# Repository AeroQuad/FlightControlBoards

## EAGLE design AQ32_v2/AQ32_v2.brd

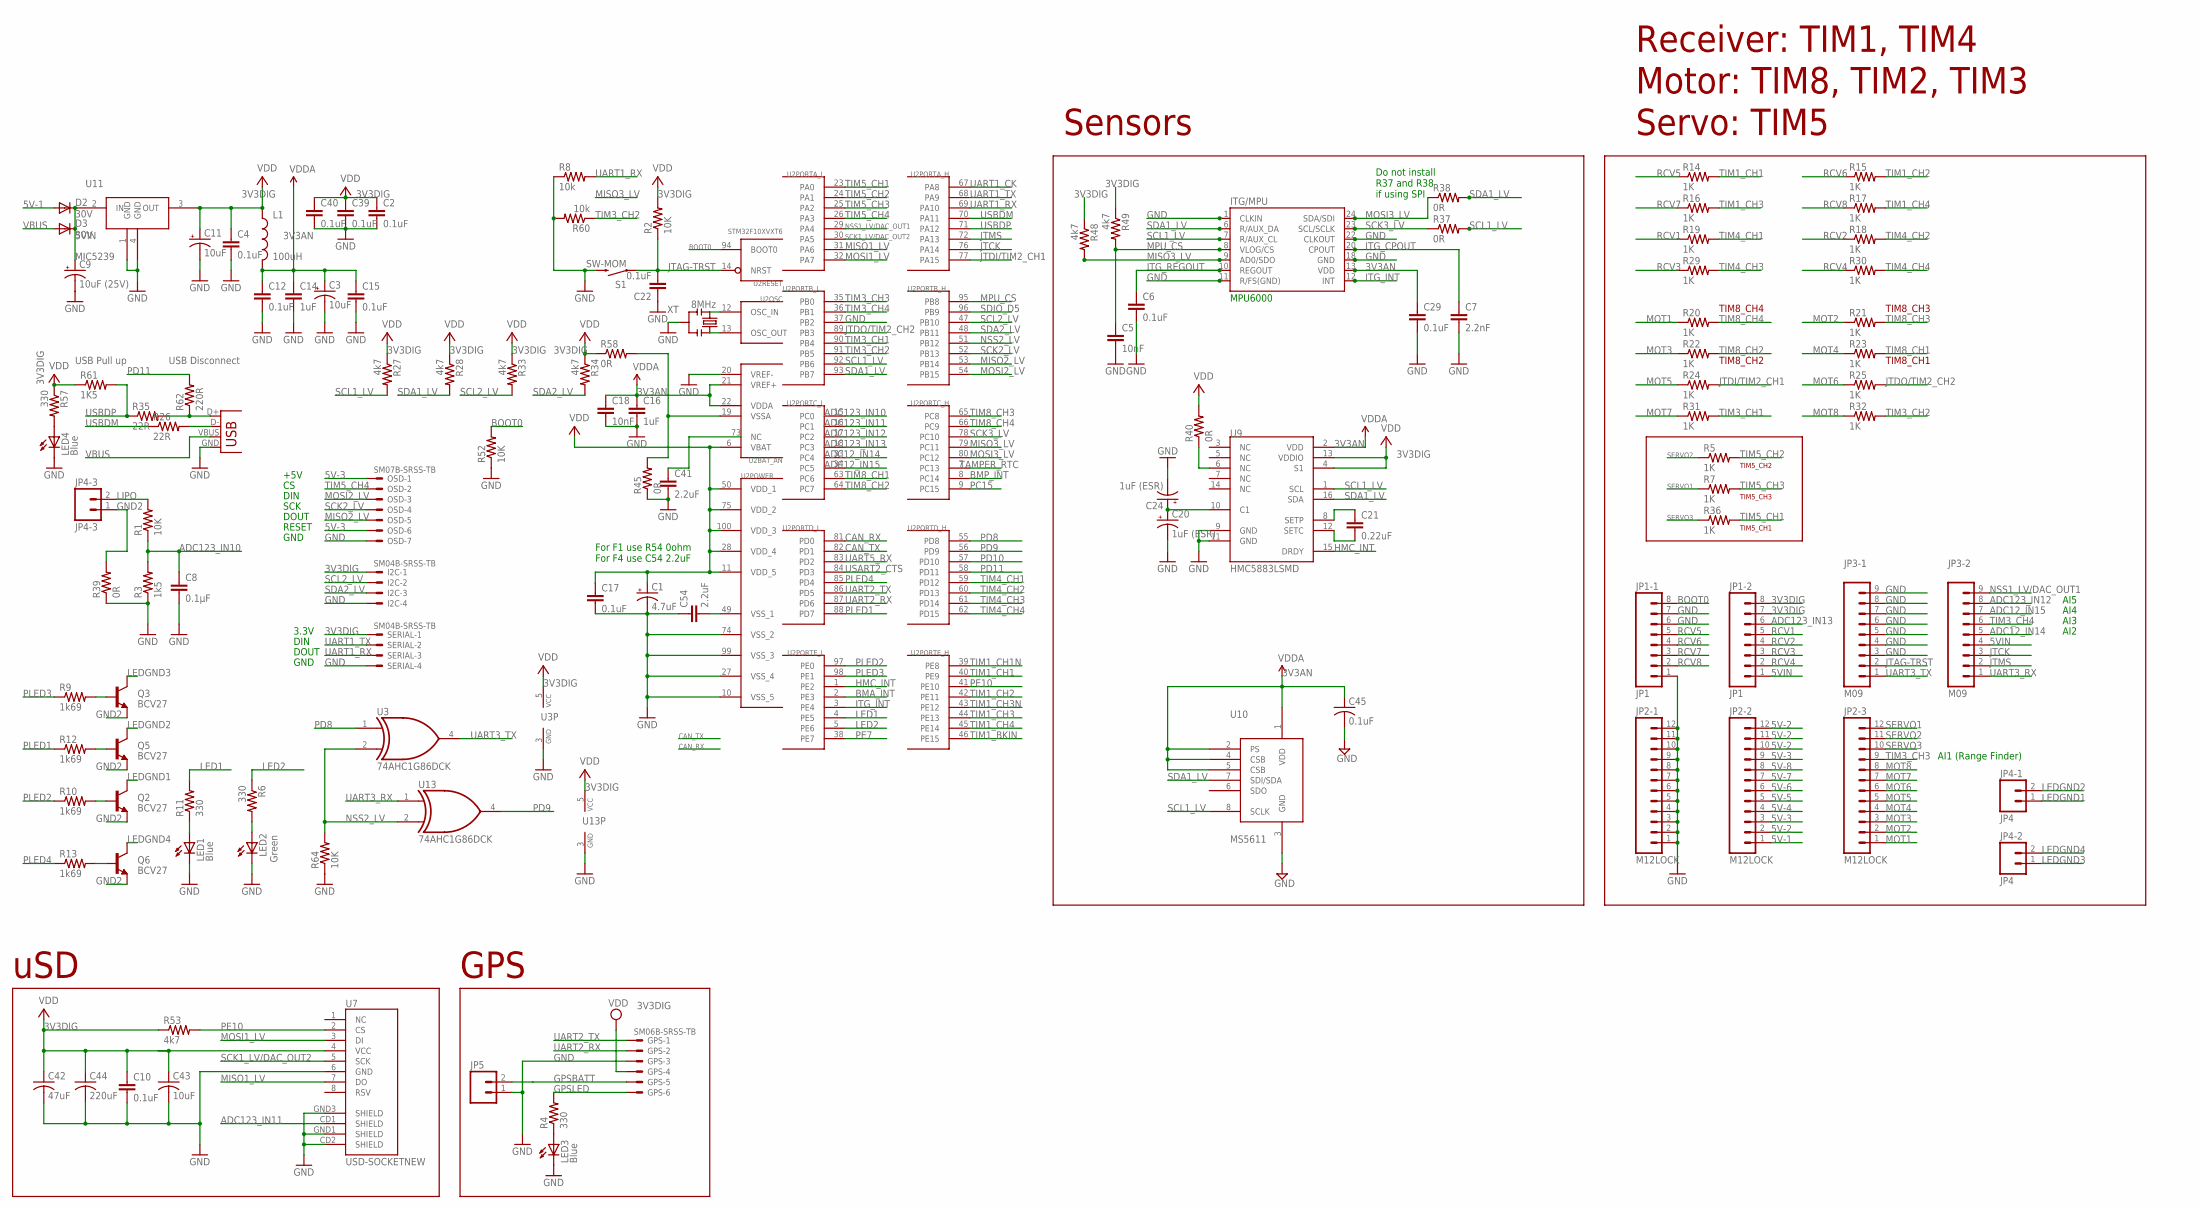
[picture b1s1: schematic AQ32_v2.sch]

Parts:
C1: 4.7uF; SMC_Z
C2, C4, C6, C10, C12, C15, C17, C22, C29, C39, C40, C45: 0.1uF; C0402
C3, C11: 10uF; EIA3216
C5, C18: 10nF; C0402
C7: 2.2nF; C0402
C8: 0.1µF; C0402
C9: 10uF (25V); EIA3216
C14, C16: 1uF; C0402
C20, C24: 1uF (ESR); SMC_Z
C21: 0.22uF; C0402
C41: 2.2uF; C0402
C42: 47uF; C0805
C43: 10uF; C0805
C44: 220uF; C1206
C54: 2.2uF; 0402-CAP
D2, D3: 30V; SOD-323
GPS: SM06B-SRSS-TB
I2C: SM04B-SRSS-TB
JP1-1, JP1-2: JP1; 1X08_LOCK
JP2-1, JP2-2, JP2-3: M12LOCK; 1X12_LOCK
JP3-1, JP3-2: M09; 1X09
JP4-1, JP4-2: JP4; 1X02
JP4-3: JP4-3; 1X02
JP5: M02PTH; 1X02
L1: 100uH; 0805
LED1, LED3, LED4: Blue; LED-0603
LED2: Green; LED-0603
OSD: SM07B-SRSS-TB
Q2, Q3, Q5, Q6: BCV27; SOT23-3
R1, R2, R52, R64: 10K; C0402
R3: 1k5; C0402
R4, R6, R11, R57: 330; C0402
R5, R7, R14, R15, R16, R17, R18, R19, R20, R21, R22, R23, R24, R25, R29, R30, R31, R32, R36: 1K; C0402
R8, R60: 10k; R0402
R9, R10, R12, R13: 1k69; C0402
R26, R35: 22R; C0402
R27, R28, R33, R34, R48, R49, R53: 4k7; C0402
R37, R38, R40, R45, R58: 0R; R0402
R39: 0R; C0402
R61: 1K5; R0402
R62: 220R; C0402
S1: SW-MOM; TACTILE_SWITCH_SMD
SERIAL: SM04B-SRSS-TB
U1: ITG-3200; QFN-24
U2: STM32F10XVXT6; TQFP100
U3, U13: 74AHC1G86DCK; SC70-5
U7: USD-SOCKETNEW; MICRO-SD-SOCKET-PP
U9: HMC5883LSMD; 16LPCC
U10: MS5611; LGA08A
U11: MIC5239; TO-223
X2: USBOLD; USB-MINIB-OLD
XT: 8MHz; RESONATOR-SMD

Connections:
3V3AN: C3.A (+), C12.1, C14.1, C15.1, C16.1, C18.1, C29.1, C45.1, L1.2, U1.13 (VDD), U2.21 (VREF+), U2.22 (VDDA), U9.2 (VDD), U10.1 (VDD), U10.2 (PS), U10.4 (CSB), U10.5 (CSB)
3V3DIG: C1.+, C2.1, C4.1, C10.1, C11.A (+), C17.1, C39.1, C40.1, C42.1, C43.1, C44.1, GPS.4, I2C.1, JP1-2.7, JP1-2.8, L1.1, R2.2, R27.1, R28.1, R33.1, R34.1, R40.2, R48.1, R49.1, R53.1, R57.1, R58.1, R61.1, SERIAL.1, U2.6 (VBAT), U2.11 (VDD_5), U2.28 (VDD_4), U2.50 (VDD_1), U2.75 (VDD_2), U2.100 (VDD_3), U3.5 (VCC), U7.4 (VCC), U9.4 (S1), U9.13 (VDDIO), U11.3 (OUT), U13.5 (VCC)
5V-1: D2.2 (A), JP2-2.1
5V-2: JP2-2.2, JP2-2.10, JP2-2.11, JP2-2.12
5V-3: JP2-2.3, JP2-2.9, OSD.1, OSD.6
5V-4: JP2-2.4
5V-5: JP2-2.5
5V-6: JP2-2.6
5V-7: JP2-2.7
5V-8: JP2-2.8
5VIN: C9.A (+), D2.1 (C), D3.1 (C), JP1-2.1, JP3-2.4, U11.2 (IN)
ADC12_IN14: JP3-2.5, U2.33 (PC4)
ADC12_IN15: JP3-2.7, U2.34 (PC5)
ADC123_IN10: C8.1, R1.1, R3.2, U2.15 (PC0)
ADC123_IN11: U2.16 (PC1), U7.CD1 (SHIELD)
ADC123_IN12: JP3-2.8, U2.17 (PC2)
ADC123_IN13: JP1-2.6, U2.18 (PC3)
BMA_INT: U2.2 (PE3)
BMP_INT: U2.8 (PC14)
BOOT0: JP1-1.8, R52.2, U2.94 (BOOT0)
CAN_RX: U2.81 (PD0)
CAN_TX: U2.82 (PD1)
GND: C1.-, C2.2, C3.C (-), C4.2, C5.2, C6.2, C7.2, C8.2, C9.C (-), C10.2, C11.C (-), C12.2, C14.2, C15.2, C16.2, C17.2, C18.2, C20.-, C22.1, C24.-, C29.2, C39.2, C40.2, C41.2, C42.2, C43.2, C44.2, C45.2, C54.1, GPS.3, I2C.4, JP1-1.1, JP1-1.6, JP1-1.7, JP2-1.1, JP2-1.2, JP2-1.3, JP2-1.4, JP2-1.5, JP2-1.6, JP2-1.7, JP2-1.8, JP2-1.9, JP2-1.10, JP2-1.11, JP2-1.12, JP3-1.3, JP3-1.4, JP3-1.5, JP3-1.6, JP3-1.7, JP3-1.8, JP3-1.9, JP5.1, LED1.C, LED2.C, LED3.C, LED4.C, OSD.7, R3.1, R8.1, R39.1, R45.1, R52.1, R60.2, R64.1, S1.3 (2), SERIAL.4, U1.1 (CLKIN), U1.11 (R/FS(GND)), U1.18 (GND), U1.22 (CLKOUT), U2.10 (VSS_5), U2.20 (VREF-), U2.27 (VSS_4), U2.37 (PB2), U2.74 (VSS_2), U2.99 (VSS_3), U3.3 (GND), U7.6 (GND)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
GND2: JP4-3.1, Q2.2 (E), Q3.2 (E), Q5.2 (E), Q6.2 (E), R39.2
GPSBATT: GPS.5, JP5.2
GPSLED: GPS.6, R4.2
HMC_INT: U2.1 (PE2), U9.15 (DRDY)
ITG_CPOUT: C7.1, U1.20 (CPOUT)
ITG_INT: U1.12 (INT), U2.3 (PE4)
ITG_REGOUT: C6.1, U1.10 (REGOUT)
JTAG-TRST: C22.2, JP3-1.2, R2.1, S1.1, U2.14 (NRST)
JTCK: JP3-2.3, U2.76 (PA14)
JTDI/TIM2_CH1: R24.2, U2.77 (PA15)
JTDO/TIM2_CH2: R25.2, U2.89 (PB3)
JTMS: JP3-2.2, U2.72 (PA13)
LED1: R11.2, U2.4 (PE5)
LED2: R6.1, U2.5 (PE6)
LEDGND1: JP4-1.1, Q2.3 (C)
LEDGND2: JP4-1.2, Q5.3 (C)
LEDGND3: JP4-2.1, Q3.3 (C)
LEDGND4: JP4-2.2, Q6.3 (C)
LIPO: JP4-3.2, R1.2
MISO1_LV: U2.31 (PA6), U7.7 (DO)
MISO2_LV: OSD.5, U2.53 (PB14)
MISO3_LV: R48.2, U1.9 (AD0/SDO), U2.79 (PC11)
MOSI1_LV: U2.32 (PA7), U7.3 (DI)
MOSI2_LV: OSD.3, U2.54 (PB15)
MOSI3_LV: R38.1, U1.24 (SDA/SDI), U2.80 (PC12)
MOT1: JP2-3.1, R20.1
MOT2: JP2-3.2, R21.1
MOT3: JP2-3.3, R22.1
MOT4: JP2-3.4, R23.1
MOT5: JP2-3.5, R24.1
MOT6: JP2-3.6, R25.1
MOT7: JP2-3.7, R31.1
MOT8: JP2-3.8, R32.1
MPU_CS: C5.1, R49.2, U1.8 (VLOG/CS), U2.95 (PB8)
unnamed: U2.12 (OSC_IN), XT.3
unnamed: U2.13 (OSC_OUT), XT.1
unnamed: LED3.A, R4.1
unnamed: R40.1, U9.6 (NC)
unnamed: LED2.A, R6.2
unnamed: Q3.1 (B), R9.2
unnamed: C54.2, U2.49 (VSS_1)
unnamed: Q2.1 (B), R10.2
unnamed: Q5.1 (B), R12.2
unnamed: LED1.A, R11.1
unnamed: Q6.1 (B), R13.2
unnamed: C41.1, U2.73 (NC)
unnamed: LED4.A, R57.2
unnamed: R45.2, R58.2, U2.19 (VSSA)
unnamed: C21.1, U9.8 (SETP)
unnamed: C21.2, U9.12 (SETC)
unnamed: C20.+, C24.+, U9.10 (C1)
unnamed: R35.2, R62.1, X2.D+
unnamed: R26.2, X2.D-
NSS1_LV/DAC_OUT1: JP3-2.9, U2.29 (PA4)
NSS2_LV: R64.2, U2.51 (PB12), U3.2 (I1), U13.2 (I1)
PC15: U2.9 (PC15)
PD8: U2.55 (PD8), U3.1 (I0)
PD9: U2.56 (PD9), U13.4 (O)
PD10: U2.57 (PD10)
PD11: R62.2, U2.58 (PD11)
PE7: U2.38 (PE7)
PE10: R53.2, U2.41 (PE10), U7.2 (CS)
PLED1: R12.1, U2.88 (PD7)
PLED2: R10.1, U2.97 (PE0)
PLED3: R9.1, U2.98 (PE1)
PLED4: R13.1, U2.85 (PD4)
RCV1: JP1-2.5, R19.1
RCV2: JP1-2.4, R18.1
RCV3: JP1-2.3, R29.1
RCV4: JP1-2.2, R30.1
RCV5: JP1-1.5, R14.1
RCV6: JP1-1.4, R15.1
RCV7: JP1-1.3, R16.1
RCV8: JP1-1.2, R17.1
SCK1_LV/DAC_OUT2: U2.30 (PA5), U7.5 (SCK)
SCK2_LV: OSD.4, U2.52 (PB13)
SCK3_LV: R37.1, U1.23 (SCL/SCLK), U2.78 (PC10)
SCL1_LV: R27.2, R37.2, U1.7 (R/AUX_CL), U2.92 (PB6), U9.1 (SCL), U10.8 (SCLK)
SCL2_LV: I2C.2, R33.2, U2.47 (PB10)
SDA1_LV: R28.2, R38.2, U1.6 (R/AUX_DA), U2.93 (PB7), U9.16 (SDA), U10.7 (SDI/SDA)
SDA2_LV: I2C.3, R34.2, U2.48 (PB11)
SDIO_D5: U2.96 (PB9)
SERVO1: JP2-3.12, R7.1
SERVO2: JP2-3.11, R5.1
SERVO3: JP2-3.10, R36.1
TAMPER_RTC: U2.7 (PC13)
TIM1_BKIN: U2.46 (PE15)
TIM1_CH1: R14.2, U2.40 (PE9)
TIM1_CH1N: U2.39 (PE8)
TIM1_CH2: R15.2, U2.42 (PE11)
TIM1_CH3: R16.2, U2.44 (PE13)
TIM1_CH3N: U2.43 (PE12)
TIM1_CH4: R17.2, U2.45 (PE14)
TIM3_CH1: R31.2, U2.90 (PB4)
TIM3_CH2: R32.2, R60.1, U2.91 (PB5)
TIM3_CH3: JP2-3.9, U2.35 (PB0)
TIM3_CH4: JP3-2.6, U2.36 (PB1)
TIM4_CH1: R19.2, U2.59 (PD12)
TIM4_CH2: R18.2, U2.60 (PD13)
TIM4_CH3: R29.2, U2.61 (PD14)
TIM4_CH4: R30.2, U2.62 (PD15)
TIM5_CH1: R36.2, U2.23 (PA0)
TIM5_CH2: R5.2, U2.24 (PA1)
TIM5_CH3: R7.2, U2.25 (PA2)
TIM5_CH4: OSD.2, U2.26 (PA3)
TIM8_CH1: R23.2, U2.63 (PC6)
TIM8_CH2: R22.2, U2.64 (PC7)
TIM8_CH3: R21.2, U2.65 (PC8)
TIM8_CH4: R20.2, U2.66 (PC9)
UART1_CK: U2.67 (PA8)
UART1_RX: R8.2, SERIAL.3, U2.69 (PA10)
UART1_TX: SERIAL.2, U2.68 (PA9)
UART2_RX: GPS.2, U2.87 (PD6)
UART2_TX: GPS.1, U2.86 (PD5)
UART3_RX: JP3-2.1, U13.1 (I0)
UART3_TX: JP3-1.1, U3.4 (O)
UART5_RX: U2.83 (PD2)
USART2_CTS: U2.84 (PD3)
USBDM: R26.1, U2.70 (PA11)
USBDP: R35.1, R61.2, U2.71 (PA12)
VBUS: D3.2 (A), X2.VBUS

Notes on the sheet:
Receiver: TIM1, TIM4
Motor: TIM8, TIM2, TIM3
Servo: TIM5
USB Pull up
USB Disconnect
MPU6000
Sensors
uSD
GPS
TIM8_CH4
TIM8_CH1
TIM8_CH3
TIM8_CH2
TIM5_CH2
TIM5_CH1
TIM5_CH3
+5V
DIN
SCK
DOUT
RESET
GND
3.3V
AI1 (Range Finder)
AI2
AI3
AI4
AI5
Do not install R37 and R38 if using SPI
For F1 use R54 0ohm For F4 use C54 2.2uF

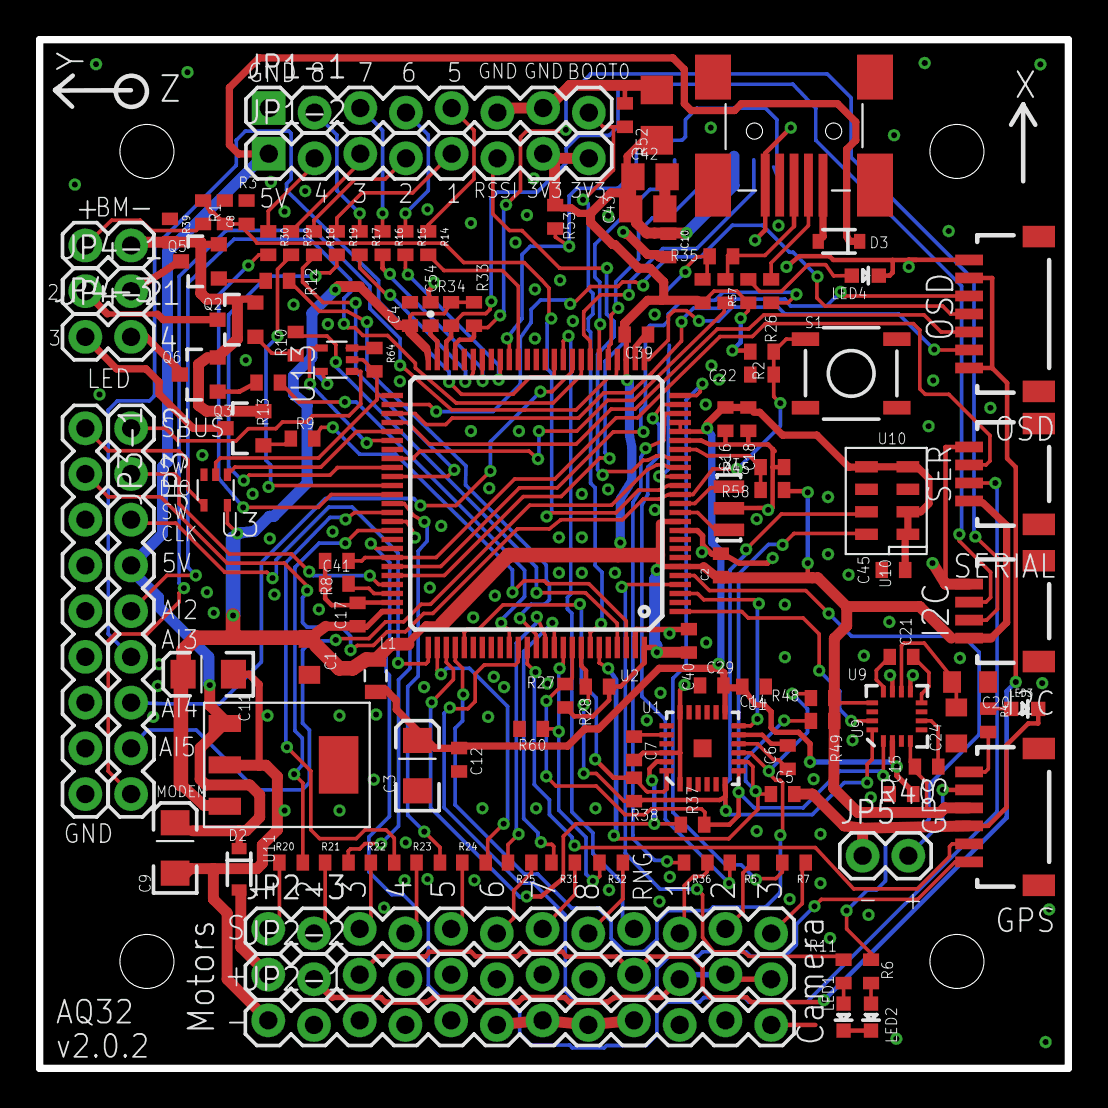
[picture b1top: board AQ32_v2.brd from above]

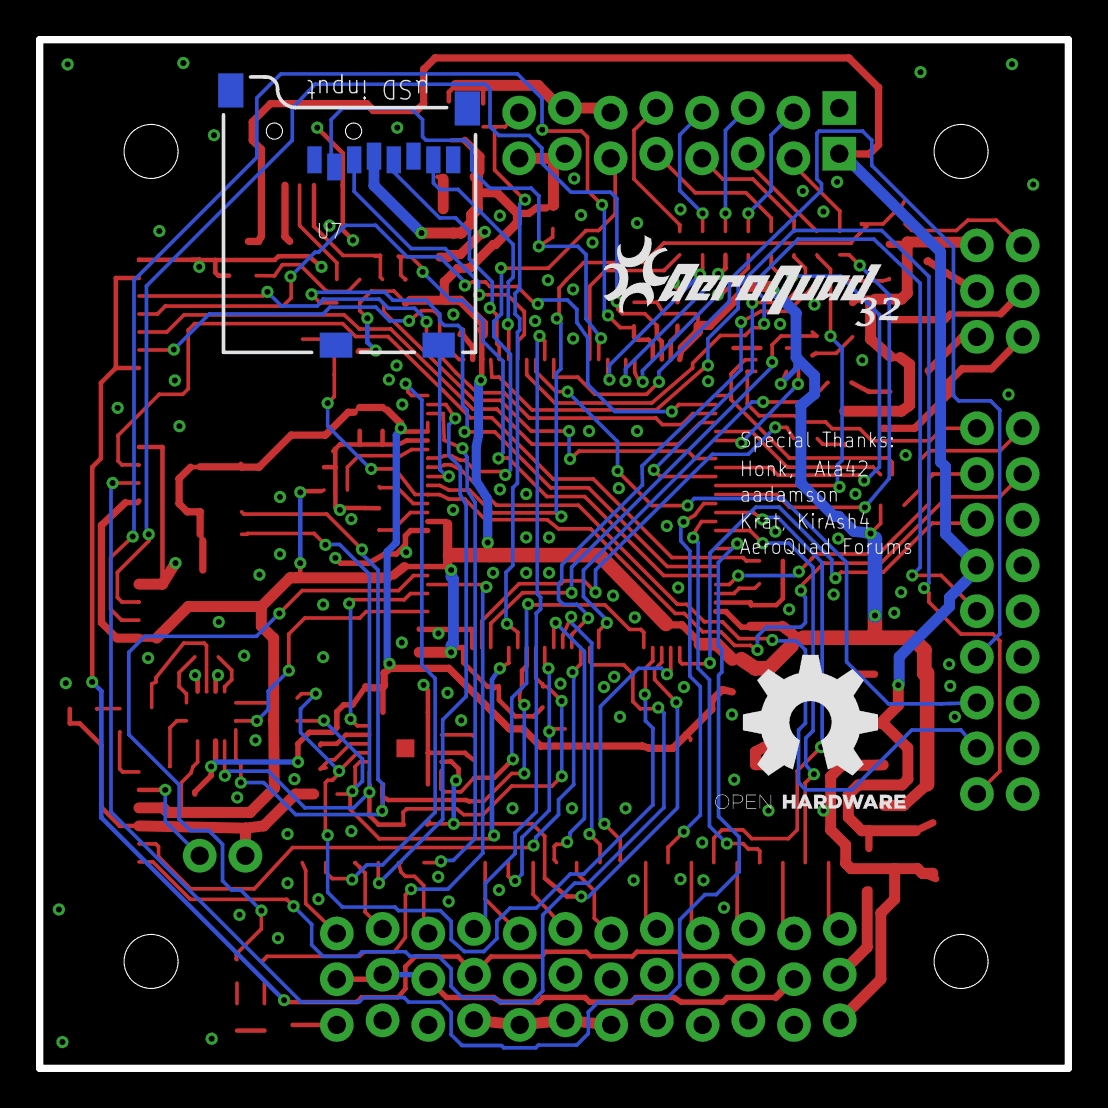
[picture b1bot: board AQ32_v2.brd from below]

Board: 2 copper layers, 57.1 x 57.1 mm, 120 parts (3 on the bottom side), 124 nets.

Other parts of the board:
U$4: AQ-WORDS-PT07
U$5: OSHW_TEXT

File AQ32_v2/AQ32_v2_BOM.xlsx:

Item # | Qty | Ref Des | Description | Package | Value | Device
1 | 2 | R54, R58 | Resistor | R0402 | 0R | R-US_R0402
2 | 6 | R1, R2, R8, R52, R60, R64 | Resistor | R0402 | 10k | RESISTOR0402
3 | 19 | R5, R7, R14, R15, R16, R17, R18, R19, R20, R21, R22, R23, R24, R25, R29, R30, R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 | Resistor | R0402 | 1k | RESISTOR0402
4 | 2 | R3, R61 | Resistor | R0402 | 1k5 | R-US_R0402
5 | 4 | R9, R10, R12, R13 | Resistor | R0402 | 1k69 | RESISTOR0402
6 | 1 | R62 | Resistor | R0402 | 220R | RESISTOR0402
7 | 2 | R26, R35 | Resistor | R0402 | 22R | RESISTOR0402
8 | 4 | R4, R6, R11, R57 | Resistor | R0402 | 330 | RESISTOR0402
9 | 7 | R27, R28, R33, R34, R48, R49, R53 | Resistor | R0402 | 4k7 | RESISTOR0402
10 | 11 | C4, C6, C8, C12, C15, C17, C22, C29, C39, C40, C45 | Capacitor | C0402 | 0.1uF | CAP0402
11 | 1 | C21 | Capacitor | C0402 | 0.22uF | CAP0402
12 | 1 | C18 | Capacitor | C0402 | 10nF | CAP0402
13 | 1 | C43 | Capacitor | C0805 | 10uF | C-USC0805
14 | 2 | C3, C11 | Capacitor Polarized | EIA3216 | 10uF | CAP_POL1206
15 | 1 | C9 | Capacitor Polarized | EIA3216 | 10uF (25V) | CAP_POL1206
16 | 2 | C14, C16 | Capacitor | C0402 | 1uF | CAP0402
17 | 2 | C20, C24 | Capacitor Polarized | SMC_Z | 1uF (ESR) | CPOL-USSMCZ
18 | 1 | C7 | Capacitor | C0402 | 2.2nF | CAP0402
19 | 1 | C41 | Capacitor | C0402 | 2.2uF | CAP0402
20 | 1 | C44 | Capacitor | C1206 | 220uF | C-USC1206
21 | 1 | C1 | Capacitor Polarized | SMC_Z | 4.7uF | CPOL-USSMCZ
22 | 1 | C42 | Capacitor | C0805 | 47uF | C-USC0805
23 | 2 | D2, D3 | Diode | SOD-323 | 30V | DIODESOD
24 | 1 | L1 | Inductors | 805 | 100uH | INDUCTOR0805
25 | 1 | L2 | Inductors | 805 | 22uH | INDUCTOR0805
26 | 1 | XT | Resonator | RESONATOR-SMD | 8MHz | RESONATORSMD
27 | 4 | Q2, Q3, Q5, Q6 | Transistor NPN | SOT23-3 | BCV27 | TRANSISTOR_NPNSOT23-3
28 | 3 | LED1, LED3, LED4 | LEDs | LED-0603 | Blue | LED0603
29 | 1 | LED2 | LEDs | LED-0603 | Green | LED0603
30 | 2 | U3, U13 | 2-input EXCLUSIV-OR gate | SC70-5 | 74AHC1G86DCK | 74AHC1G86DCK
31 | 1 | U9 | 3 Axis Digital Compass IC | 16LPCC | HMC5883LSMD | HMC5883LSMD
32 | 1 | U11 | LDO 3.3V Volt Reg | TO-223 | MIC5239 | MIC5239
33 | 2 | I2C, SERIAL | Disconnectable Crimp style connector, 1.0mm pitch4 contacts | SM04B-SRSS-TB | SM04B-SRSS-TB | SM04B-SRSS-TB
34 | 1 | GPS | Disconnectable Crimp style connector, 1.0mm pitch6 contacts | SM06B-SRSS-TB | SM06B-SRSS-TB | SM06B-SRSS-TB
35 | 1 | OSD | Disconnectable Crimp style connector, 1.0mm pitch7 contacts | SM07B-SRSS-TB | SM07B-SRSS-TB | SM07B-SRSS-TB
36 | 1 | U2 | STM32F407VGT6 | TQFP100 | STM32F407VGT6 | STM32F407VGT6
37 | 1 | S1 | SWITCH TACTILE SPST-NO 0.05A 12V | TACTILE_SWITCH_SMD | SW-MOM | SWITCH-MOMENTARY-2SMD
38 | 1 | X2 | USB Connectors | USB-MINIB-OLD | USBOLD | USBOLD
39 | 1 | U7 | microSD Socket | MICRO-SD-SOCKET-PP | USD-SOCKETNEW | USD-SOCKETNEW
40 | 1 | JP1 | 2x8 Right Angle Male Header | 2x08 | JP1 | M08LOCK
41 | 1 | JP3-1, JP3-2 | Do Not Install | Do Not Install | Do Not Install | Do Not Install
42 | 1 | JP4-1, JP4-2 | Do Not Install | Do Not Install | Do Not Install | Do Not Install
43 | 2 | JP5, JP6 | Do Not Install | Do Not Install | Do Not Install | Do Not Install
44 | 1 | C5 | Do Not Install | Do Not Install | Do Not Install | Do Not Install
45 | 2 | R37, R38, R45 | Do Not Install | Do Not Install | Do Not Install | Do Not Install
46 | 1 | JP2 | 3x12 Right Angle Male Header | 3x12 | M12LOCK | M12LOCK
47 | 1 | U1 | MPU-6000 6DOF IMU | QFN-24 | MPU-6000 | MPU-6000
48 | 1 | U10 | Pressure sensor 10cm | LGA08A | MS5611 | MS5611

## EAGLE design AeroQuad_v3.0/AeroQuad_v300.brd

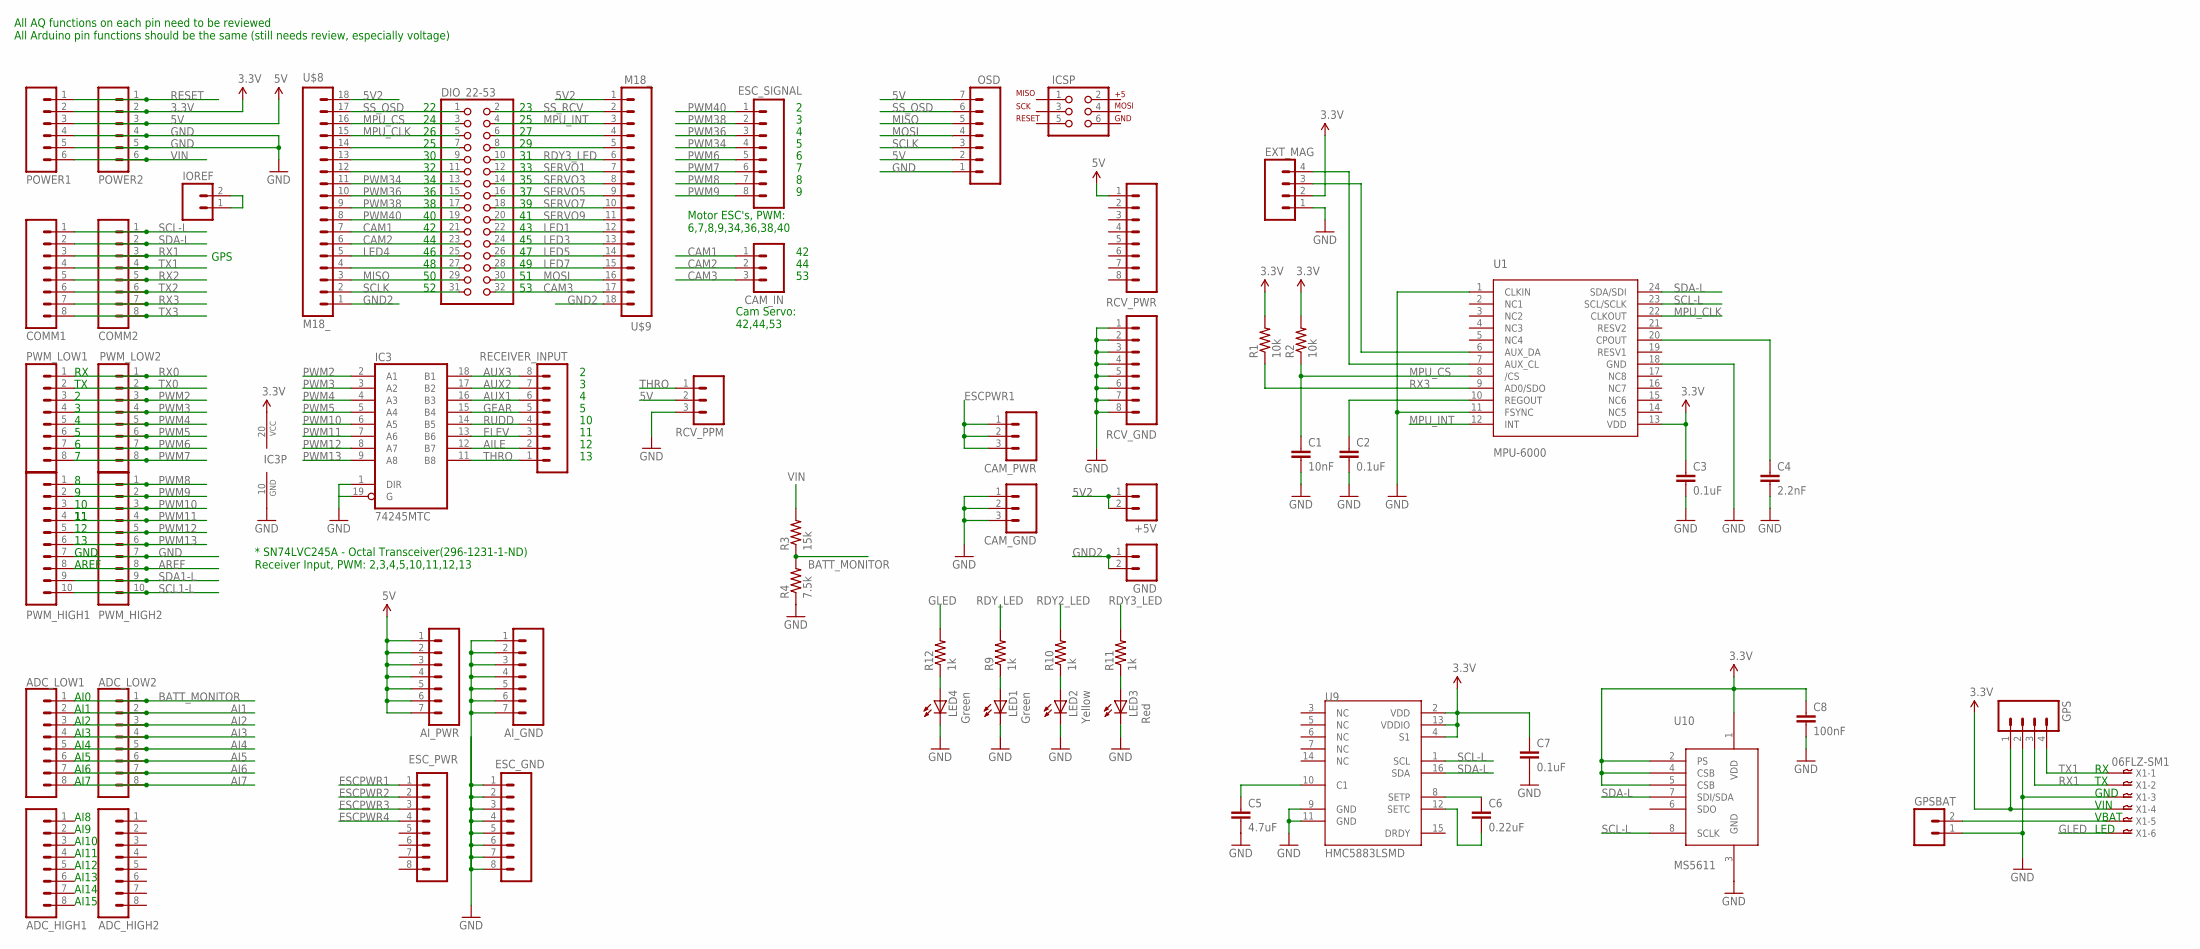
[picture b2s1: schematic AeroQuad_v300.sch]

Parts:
+5V: M02PTH; 1X02
ADC_HIGH1, ADC_HIGH2: M08LOCK; 1X08_LOCK
ADC_LOW1, ADC_LOW2: M08LOCK; 1X08_LOCK
AI_GND: M07; 1X07
AI_PWR: M07; 1X07
C1: 10nF; 0402-CAP
C2, C3, C7: 0.1uF; 0402-CAP
C4: 2.2nF; 0402-CAP
C5: 4.7uF; 0402-CAP
C6: 0.22uF; 0402-CAP
C8: 100nF; 0402-CAP
CAM_GND: M03LOCK; 1X03_LOCK
CAM_IN: M03LOCK; 1X03_LOCK
CAM_PWR: M03LOCK; 1X03_LOCK
COMM1, COMM2: M08LOCK; 1X08_LOCK
DIO_22-53: PINHD-2X16; 2X16
ESC_GND: M11LOCK; 1X08_LOCK
ESC_PWR: M11LOCK; 1X08_LOCK
ESC_SIGNAL: M11LOCK; 1X08_LOCK
EXT_MAG: M04LOCK; 1X04_LOCK
GND: M02PTH; 1X02
GPS: M04LOCK; 1X04_LOCK
GPSBAT: M02PTH; 1X02
IC3: 74245MTC; SSOP20
ICSP: AVR_SPI_PRG_6NS; 2X3-NS
IOREF: M02LOCK; 1X02_LOCK
LED1, LED4: Green; LED-0603
LED2: Yellow; LED-0603
LED3: Red; LED-0603
OSD: M07LOCK; 1X07_LOCK
POWER1, POWER2: M06LOCK; 1X06_LOCK
PWM_HIGH1, PWM_HIGH2: M10LOCK; 1X10_LOCK
PWM_LOW1, PWM_LOW2: M08LOCK; 1X08_LOCK
R1, R2: 10k; 0402-RES
R3: 15k; 0402-RES
R4: 7.5k; 0402-RES
R9, R10, R11, R12: 1k; 0402-RES
RCV_GND: M10LOCK; 1X08_LOCK
RCV_PPM: M03LOCK; 1X03_LOCK
RCV_PWR: M10LOCK; 1X08_LOCK
RECEIVER_INPUT: M08LOCK; 1X08_LOCK
U1: MPU-6000; QFN-24
U9: HMC5883LSMD; 16LPCC
U10: MS5611; LGA08A
U$8, U$9: M18_; 1X18
X1: 06FLZ-SM1; 6FLZ-SM

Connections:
3.3V: C3.1, C7.1, C8.1, EXT_MAG.2, GPS.1, IC3.20 (VCC), POWER1.2, POWER2.2, R1.2, R2.2, U1.13 (VDD), U9.2 (VDD), U9.4 (S1), U9.13 (VDDIO), U10.1 (VDD), U10.2 (PS), U10.4 (CSB), U10.5 (CSB), X1.4
5V: AI_PWR.1, AI_PWR.2, AI_PWR.3, AI_PWR.4, AI_PWR.5, AI_PWR.6, AI_PWR.7, OSD.2, OSD.7, POWER1.3, POWER2.3, RCV_PPM.2, RCV_PWR.1
5V2: +5V.1, +5V.2, U$8.18, U$9.1
AI1: ADC_LOW1.2, ADC_LOW2.2
AI2: ADC_LOW1.3, ADC_LOW2.3
AI3: ADC_LOW1.4, ADC_LOW2.4
AI4: ADC_LOW1.5, ADC_LOW2.5
AI5: ADC_LOW1.6, ADC_LOW2.6
AI6: ADC_LOW1.7, ADC_LOW2.7
AI7: ADC_LOW1.8, ADC_LOW2.8
AILE: IC3.12 (B7), RECEIVER_INPUT.2
AREF: PWM_HIGH1.8, PWM_HIGH2.8
AUX1: IC3.16 (B3), RECEIVER_INPUT.6
AUX2: IC3.17 (B2), RECEIVER_INPUT.7
AUX3: IC3.18 (B1), RECEIVER_INPUT.8
BATT_MONITOR: ADC_LOW1.1, ADC_LOW2.1, R3.1, R4.2
CAM1: CAM_IN.1, DIO_22-53.21, U$8.7
CAM2: CAM_IN.2, DIO_22-53.23, U$8.6
CAM3: CAM_IN.3, DIO_22-53.32, U$9.17
ELEV: IC3.13 (B6), RECEIVER_INPUT.3
ESCPWR1: CAM_PWR.1, CAM_PWR.2, CAM_PWR.3, ESC_PWR.1
ESCPWR2: ESC_PWR.2
ESCPWR3: ESC_PWR.3
ESCPWR4: ESC_PWR.4
GEAR: IC3.15 (B4), RECEIVER_INPUT.5
GLED: R12.2, X1.6
GND: AI_GND.1, AI_GND.2, AI_GND.3, AI_GND.4, AI_GND.5, AI_GND.6, AI_GND.7, C1.2, C2.2, C3.2, C4.2, C5.2, C7.2, C8.2, CAM_GND.1, CAM_GND.2, CAM_GND.3, ESC_GND.1, ESC_GND.2, ESC_GND.3, ESC_GND.4, ESC_GND.5, ESC_GND.6, ESC_GND.7, ESC_GND.8, EXT_MAG.1, GPS.2, GPSBAT.1, IC3.1 (DIR), IC3.10 (GND), IC3.19 (G), LED1.C, LED2.C, LED3.C, LED4.C, OSD.1, POWER1.4, POWER1.5, POWER2.4, POWER2.5, PWM_HIGH1.7, PWM_HIGH2.7, R4.1, RCV_GND.1, RCV_GND.2, RCV_GND.3, RCV_GND.4, RCV_GND.5, RCV_GND.6, RCV_GND.7, RCV_GND.8, RCV_PPM.3, U1.1 (CLKIN), U1.11 (FSYNC), U1.18 (GND), U9.9 (GND), U9.11 (GND), U10.3 (GND), X1.3
GND2: GND.1, GND.2, U$8.1, U$9.18
LED1: DIO_22-53.22, U$9.12
LED3: DIO_22-53.24, U$9.13
LED4: DIO_22-53.25, U$8.5
LED5: DIO_22-53.26, U$9.14
LED7: DIO_22-53.28, U$9.15
MISO: DIO_22-53.29, OSD.5, U$8.3
MOSI: DIO_22-53.30, OSD.4, U$9.16
MPU_CLK: DIO_22-53.5, U1.22 (CLKOUT), U$8.15
MPU_CS: C1.1, DIO_22-53.3, R2.1, U1.8 (/CS), U$8.16
MPU_INT: DIO_22-53.4, U1.12 (INT), U$9.3
unnamed: DIO_22-53.11, U$8.12
unnamed: DIO_22-53.9, U$8.13
unnamed: DIO_22-53.7, U$8.14
unnamed: LED4.A, R12.1
unnamed: DIO_22-53.27, U$8.4
unnamed: GPSBAT.2, X1.5
unnamed: LED1.A, R9.1
unnamed: LED2.A, R10.1
unnamed: LED3.A, R11.1
unnamed: C5.1, U9.10 (C1)
unnamed: EXT_MAG.4, U1.7 (AUX_CL)
unnamed: EXT_MAG.3, U1.6 (AUX_DA)
unnamed: IOREF.1, IOREF.2
unnamed: C6.1, U9.8 (SETP)
unnamed: C6.2, U9.12 (SETC)
unnamed: C2.1, U1.10 (REGOUT)
unnamed: DIO_22-53.6, U$9.4
unnamed: DIO_22-53.8, U$9.5
unnamed: C4.1, U1.20 (CPOUT)
PWM2: IC3.2 (A1), PWM_LOW1.3, PWM_LOW2.3
PWM3: IC3.3 (A2), PWM_LOW1.4, PWM_LOW2.4
PWM4: IC3.4 (A3), PWM_LOW1.5, PWM_LOW2.5
PWM5: IC3.5 (A4), PWM_LOW1.6, PWM_LOW2.6
PWM6: ESC_SIGNAL.5, PWM_LOW1.7, PWM_LOW2.7
PWM7: ESC_SIGNAL.6, PWM_LOW1.8, PWM_LOW2.8
PWM8: ESC_SIGNAL.7, PWM_HIGH1.1, PWM_HIGH2.1
PWM9: ESC_SIGNAL.8, PWM_HIGH1.2, PWM_HIGH2.2
PWM10: IC3.6 (A5), PWM_HIGH1.3, PWM_HIGH2.3
PWM11: IC3.7 (A6), PWM_HIGH1.4, PWM_HIGH2.4
PWM12: IC3.8 (A7), PWM_HIGH1.5, PWM_HIGH2.5
PWM13: IC3.9 (A8), PWM_HIGH1.6, PWM_HIGH2.6
PWM34: DIO_22-53.13, ESC_SIGNAL.4, U$8.11
PWM36: DIO_22-53.15, ESC_SIGNAL.3, U$8.10
PWM38: DIO_22-53.17, ESC_SIGNAL.2, U$8.9
PWM40: DIO_22-53.19, ESC_SIGNAL.1, U$8.8
RDY2_LED: R10.2
RDY3_LED: DIO_22-53.10, R11.2, U$9.6
RDY_LED: R9.2
RESET: POWER1.1, POWER2.1
RUDD: IC3.14 (B5), RECEIVER_INPUT.4
RX0: PWM_LOW1.1, PWM_LOW2.1
RX1: COMM1.3, COMM2.3, GPS.3, X1.2
RX2: COMM1.5, COMM2.5
RX3: COMM1.7, COMM2.7, R1.1, U1.9 (AD0/SDO)
SCL1-L: PWM_HIGH1.10, PWM_HIGH2.10
SCL-L: COMM1.1, COMM2.1, U1.23 (SCL/SCLK), U9.1 (SCL), U10.8 (SCLK)
SCLK: DIO_22-53.31, OSD.3, U$8.2
SDA1-L: PWM_HIGH1.9, PWM_HIGH2.9
SDA-L: COMM1.2, COMM2.2, U1.24 (SDA/SDI), U9.16 (SDA), U10.7 (SDI/SDA)
SERVO1: DIO_22-53.12, U$9.7
SERVO3: DIO_22-53.14, U$9.8
SERVO5: DIO_22-53.16, U$9.9
SERVO7: DIO_22-53.18, U$9.10
SERVO9: DIO_22-53.20, U$9.11
SS_OSD: DIO_22-53.1, OSD.6, U$8.17
SS_RCV: DIO_22-53.2, U$9.2
THRO: IC3.11 (B8), RCV_PPM.1, RECEIVER_INPUT.1
TX0: PWM_LOW1.2, PWM_LOW2.2
TX1: COMM1.4, COMM2.4, GPS.4, X1.1
TX2: COMM1.6, COMM2.6
TX3: COMM1.8, COMM2.8
VIN: POWER1.6, POWER2.6, R3.2

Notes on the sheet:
GND
AREF
AI0
AI1
AI2
AI3
AI4
AI5
AI6
AI7
AI8
AI9
AI10
AI11
AI12
AI13
AI14
AI15
GPS
VIN
VBAT
LED
* SN74LVC245A - Octal Transceiver(296-1231-1-ND) Receiver Input, PWM: 2,3,4,5,10,11,12,13
Motor ESC's, PWM: 6,7,8,9,34,36,38,40
All AQ functions on each pin need to be reviewed All Arduino pin functions should be the same (still needs review, especially voltage)
Cam Servo: 42,44,53

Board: 2 copper layers, 60 parts (0 on the bottom side), 95 nets, no tracks yet.

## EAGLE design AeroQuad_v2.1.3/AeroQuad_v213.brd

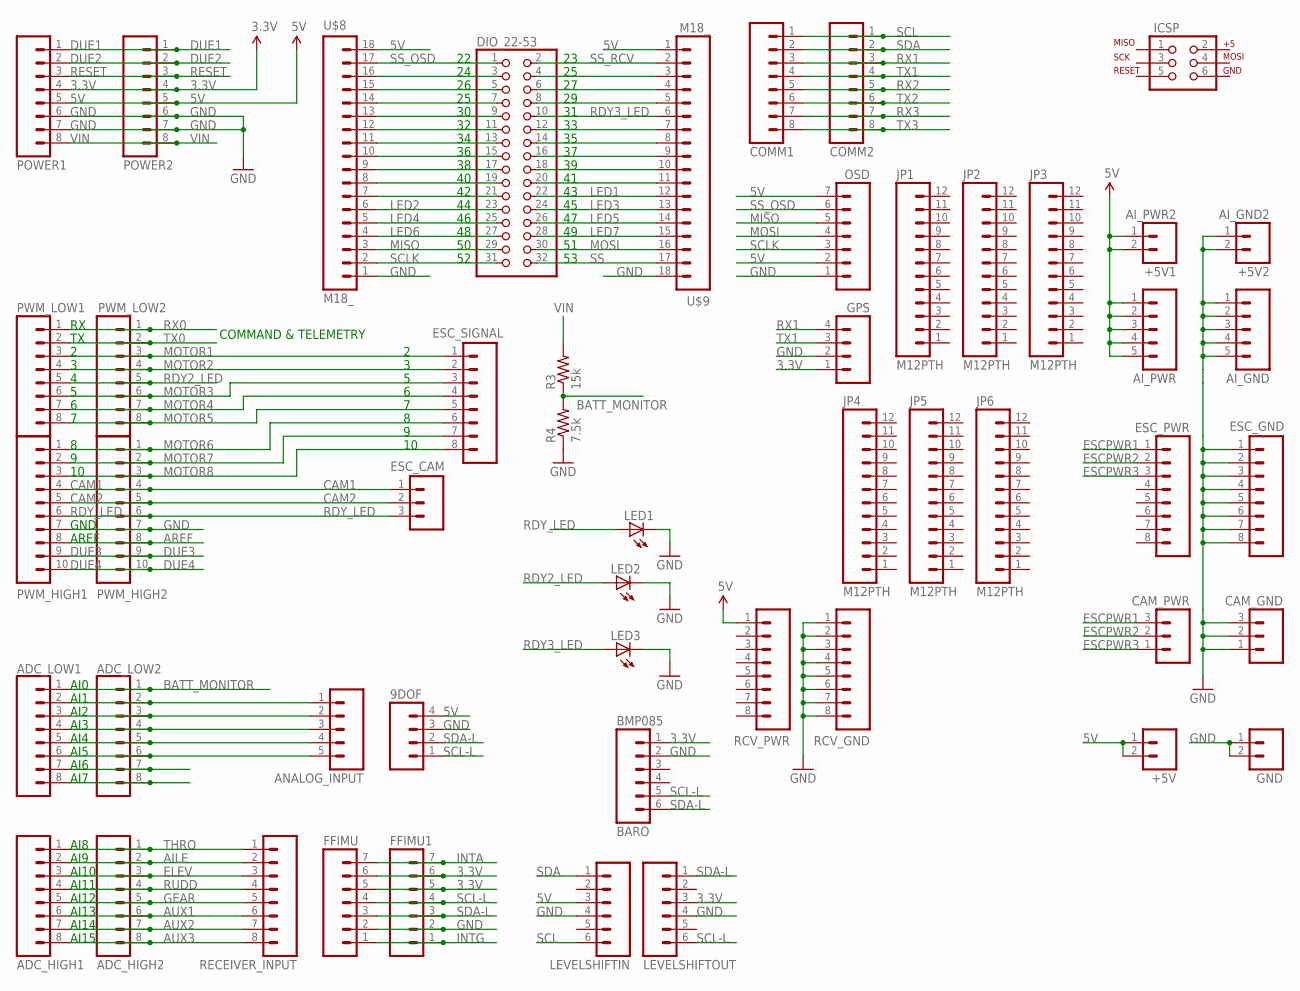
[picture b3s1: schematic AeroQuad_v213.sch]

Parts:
9DOF: M04LOCK; 1X04_LOCK
+5V: M02PTH; 1X02
+5V1: AI_PWR2; 1X02
+5V2: AI_GND2; 1X02
ADC_HIGH1, ADC_HIGH2: M08LOCK; 1X08_LOCK
ADC_LOW1, ADC_LOW2: M08LOCK; 1X08_LOCK
AI_GND: M05LOCK; 1X05_LOCK
AI_PWR: M05LOCK; 1X05_LOCK
ANALOG_INPUT: M05LOCK; 1X05_LOCK
BARO: BMP085; 1X06_LOCK
CAM_GND: M03LOCK; 1X03_LOCK
CAM_PWR: M03LOCK; 1X03_LOCK
COMM1, COMM2: M08LOCK; 1X08_LOCK
DIO_22-53: PINHD-2X16; 2X16
ESC_CAM: M03LOCK; 1X03_LOCK
ESC_GND: M10LOCK; 1X08_LOCK
ESC_PWR: M10LOCK; 1X08_LOCK
ESC_SIGNAL: M10LOCK; 1X08_LOCK
FFIMU, FFIMU1: M07LOCK; 1X07_LOCK
GND: M02PTH; 1X02
GPS: M04LOCK; 1X04_LOCK
ICSP: AVR_SPI_PRG_6NS; 2X3-NS
JP1, JP2, JP3, JP4, JP5, JP6: M12PTH; 1X12
LED1, LED2, LED3: LED5MM
LEVELSHIFTIN: M06LOCK; 1X06_LOCK
LEVELSHIFTOUT: M06LOCK; 1X06_LOCK
OSD: M07LOCK; 1X07_LOCK
POWER1, POWER2: M08LOCK; 1X08_LOCK
PWM_HIGH1, PWM_HIGH2: M10LOCK; 1X10_LOCK
PWM_LOW1, PWM_LOW2: M08LOCK; 1X08_LOCK
R3: 15k; 0204/5
R4: 7.5k; 0204/5
RCV_GND: M10LOCK; 1X08_LOCK
RCV_PWR: M10LOCK; 1X08_LOCK
RECEIVER_INPUT: M08LOCK; 1X08_LOCK
U$8, U$9: M18_; 1X18

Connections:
3.3V: BARO.1, FFIMU.5, FFIMU.6, FFIMU1.5, FFIMU1.6, GPS.1, LEVELSHIFTOUT.3, POWER1.4, POWER2.4
5V: 9DOF.4, +5V.1, +5V.2, +5V1.1, +5V1.2, AI_PWR.1, AI_PWR.2, AI_PWR.3, AI_PWR.4, AI_PWR.5, LEVELSHIFTIN.3, OSD.2, OSD.7, POWER1.5, POWER2.5, RCV_PWR.1, U$8.18, U$9.1
AILE: ADC_HIGH1.2, ADC_HIGH2.2, RECEIVER_INPUT.2
AREF: PWM_HIGH1.8, PWM_HIGH2.8
AUX1: ADC_HIGH1.6, ADC_HIGH2.6, RECEIVER_INPUT.6
AUX2: ADC_HIGH1.7, ADC_HIGH2.7, RECEIVER_INPUT.7
AUX3: ADC_HIGH1.8, ADC_HIGH2.8, RECEIVER_INPUT.8
BATT_MONITOR: ADC_LOW1.1, ADC_LOW2.1, R3.1, R4.2
CAM1: ESC_CAM.1, PWM_HIGH1.4, PWM_HIGH2.4
CAM2: ESC_CAM.2, PWM_HIGH1.5, PWM_HIGH2.5
DUE1: POWER1.1, POWER2.1
DUE2: POWER1.2, POWER2.2
DUE3: PWM_HIGH1.9, PWM_HIGH2.9
DUE4: PWM_HIGH1.10, PWM_HIGH2.10
ELEV: ADC_HIGH1.3, ADC_HIGH2.3, RECEIVER_INPUT.3
ESCPWR1: CAM_PWR.3, ESC_PWR.1
ESCPWR2: CAM_PWR.2, ESC_PWR.2
ESCPWR3: CAM_PWR.1, ESC_PWR.3
GEAR: ADC_HIGH1.5, ADC_HIGH2.5, RECEIVER_INPUT.5
GND: 9DOF.3, +5V2.1, +5V2.2, AI_GND.1, AI_GND.2, AI_GND.3, AI_GND.4, AI_GND.5, BARO.2, CAM_GND.1, CAM_GND.2, CAM_GND.3, ESC_GND.1, ESC_GND.2, ESC_GND.3, ESC_GND.4, ESC_GND.5, ESC_GND.6, ESC_GND.7, ESC_GND.8, FFIMU.2, FFIMU1.2, GND.1, GND.2, GPS.2, LED1.K (C), LED2.K (C), LED3.K (C), LEVELSHIFTIN.4, LEVELSHIFTOUT.4, OSD.1, POWER1.6, POWER1.7, POWER2.6, POWER2.7, PWM_HIGH1.7, PWM_HIGH2.7, R4.1, RCV_GND.1, RCV_GND.2, RCV_GND.3, RCV_GND.4, RCV_GND.5, RCV_GND.6, RCV_GND.7, RCV_GND.8, U$8.1, U$9.18
INTA: FFIMU.7, FFIMU1.7
INTG: FFIMU.1, FFIMU1.1
LED1: DIO_22-53.22, U$9.12
LED2: DIO_22-53.23, U$8.6
LED3: DIO_22-53.24, U$9.13
LED4: DIO_22-53.25, U$8.5
LED5: DIO_22-53.26, U$9.14
LED6: DIO_22-53.27, U$8.4
LED7: DIO_22-53.28, U$9.15
MISO: DIO_22-53.29, OSD.5, U$8.3
MOSI: DIO_22-53.30, OSD.4, U$9.16
MOTOR1: ESC_SIGNAL.1, PWM_LOW1.3, PWM_LOW2.3
MOTOR2: ESC_SIGNAL.2, PWM_LOW1.4, PWM_LOW2.4
MOTOR3: ESC_SIGNAL.3, PWM_LOW1.6, PWM_LOW2.6
MOTOR4: ESC_SIGNAL.4, PWM_LOW1.7, PWM_LOW2.7
MOTOR5: ESC_SIGNAL.5, PWM_LOW1.8, PWM_LOW2.8
MOTOR6: ESC_SIGNAL.6, PWM_HIGH1.1, PWM_HIGH2.1
MOTOR7: ESC_SIGNAL.7, PWM_HIGH1.2, PWM_HIGH2.2
MOTOR8: ESC_SIGNAL.8, PWM_HIGH1.3, PWM_HIGH2.3
unnamed: DIO_22-53.11, U$8.12
unnamed: DIO_22-53.9, U$8.13
unnamed: DIO_22-53.7, U$8.14
unnamed: ADC_LOW1.2, ADC_LOW2.2, ANALOG_INPUT.1
unnamed: ADC_LOW1.3, ADC_LOW2.3, ANALOG_INPUT.2
unnamed: ADC_LOW1.4, ADC_LOW2.4, ANALOG_INPUT.3
unnamed: ADC_LOW1.5, ADC_LOW2.5, ANALOG_INPUT.4
unnamed: ADC_LOW1.6, ADC_LOW2.6, ANALOG_INPUT.5
unnamed: DIO_22-53.3, U$8.16
unnamed: ADC_LOW1.7, ADC_LOW2.7
unnamed: ADC_LOW1.8, ADC_LOW2.8
unnamed: DIO_22-53.5, U$8.15
unnamed: DIO_22-53.4, U$9.3
unnamed: DIO_22-53.6, U$9.4
unnamed: DIO_22-53.8, U$9.5
RDY2_LED: LED2.A, PWM_LOW1.5, PWM_LOW2.5
RDY3_LED: DIO_22-53.10, LED3.A, U$9.6
RDY_LED: ESC_CAM.3, LED1.A, PWM_HIGH1.6, PWM_HIGH2.6
RESET: POWER1.3, POWER2.3
RUDD: ADC_HIGH1.4, ADC_HIGH2.4, RECEIVER_INPUT.4
RX0: PWM_LOW1.1, PWM_LOW2.1
RX1: COMM1.3, COMM2.3, GPS.4
RX2: COMM1.5, COMM2.5
RX3: COMM1.7, COMM2.7
SCL: COMM1.1, COMM2.1, LEVELSHIFTIN.6
SCL-L: 9DOF.1, BARO.5, FFIMU.4, FFIMU1.4, LEVELSHIFTOUT.6
SCLK: DIO_22-53.31, OSD.3, U$8.2
SDA: COMM1.2, COMM2.2, LEVELSHIFTIN.1
SDA-L: 9DOF.2, BARO.6, FFIMU.3, FFIMU1.3, LEVELSHIFTOUT.1
SERVO1: DIO_22-53.12, U$9.7
SERVO2: DIO_22-53.13, U$8.11
SERVO3: DIO_22-53.14, U$9.8
SERVO4: DIO_22-53.15, U$8.10
SERVO5: DIO_22-53.16, U$9.9
SERVO6: DIO_22-53.17, U$8.9
SERVO7: DIO_22-53.18, U$9.10
SERVO8: DIO_22-53.19, U$8.8
SERVO9: DIO_22-53.20, U$9.11
SERVO10: DIO_22-53.21, U$8.7
SS: DIO_22-53.32, U$9.17
SS_OSD: DIO_22-53.1, OSD.6, U$8.17
SS_RCV: DIO_22-53.2, U$9.2
THRO: ADC_HIGH1.1, ADC_HIGH2.1, RECEIVER_INPUT.1
TX0: PWM_LOW1.2, PWM_LOW2.2
TX1: COMM1.4, COMM2.4, GPS.3
TX2: COMM1.6, COMM2.6
TX3: COMM1.8, COMM2.8
VIN: POWER1.8, POWER2.8, R3.2

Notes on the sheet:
GND
AREF
AI0
AI1
AI2
AI3
AI4
AI5
AI6
AI7
AI8
AI9
AI10
AI11
AI12
AI13
AI14
AI15
COMMAND & TELEMETRY

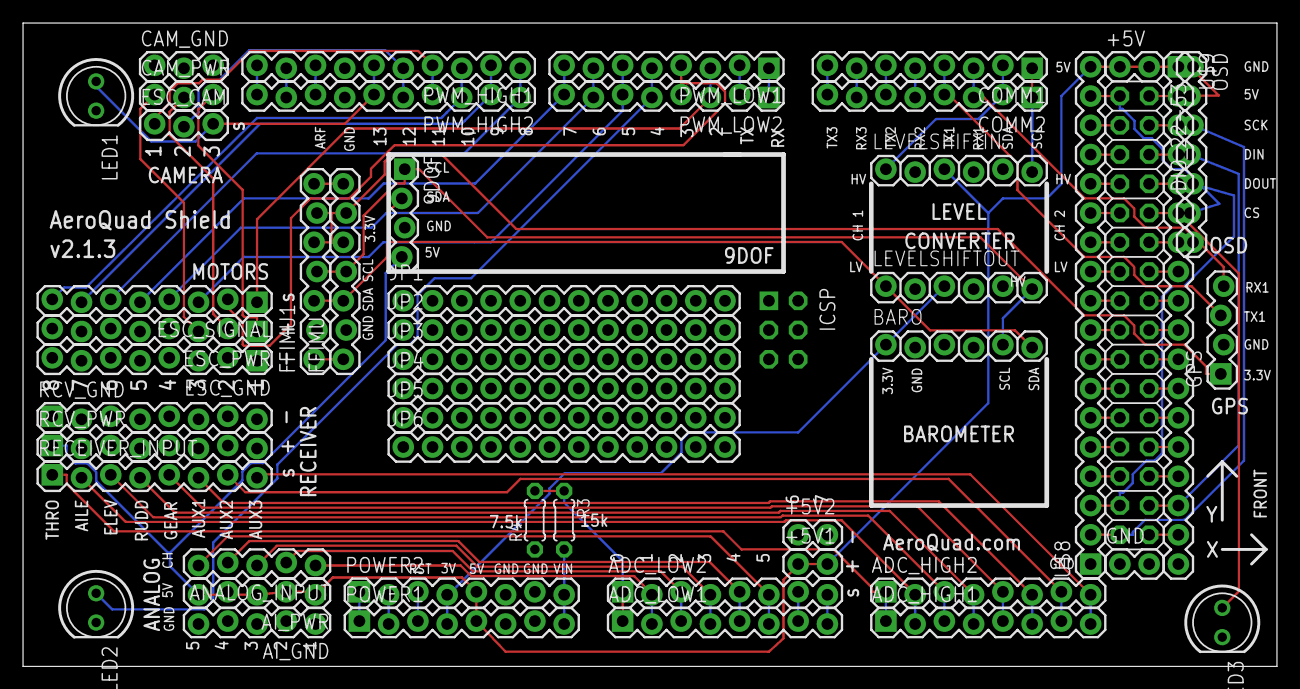
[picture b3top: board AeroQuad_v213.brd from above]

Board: 2 copper layers, 108.9 x 55.9 mm, 51 parts (0 on the bottom side), 87 nets.

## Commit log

2012-01-07 Initial Check In
2012-01-07 folder cleanup
2012-05-31 AeroQuad 32 Board Eagle Files
2012-06-01 adding BOM for AeroQuad 32 board
2012-06-11 Eagle files including CAM file for latest beta run of AeroQuad32 boards.
2012-06-28 reviewed MPU6000 circuit and connections to Due
2012-07-03 updated v2.1.3 shield with fixed 3.3V for GPS and added 5V reset line for OSD
2012-07-03 added pdf documentation
2012-07-03 removing uneeded files
2012-08-08 fixed LED driver bug, added support for SBUS and fixed GPS connector pinout
2013-04-08 Initial Check In for AQ32 v2
2013-04-13 completed connections to external JST connectors
2013-04-15 move LEDs to separate connector, connected baro to SPI
2013-04-15 added ground pin for GPS battery
2013-04-15 converted baro back to using I2C, renamed TX4/TX5 to use I2C3 labels
2013-04-17 fixed airwires
2013-04-17 fixed clearance issues
2013-04-17 Beefed up +5V in and ground traces
2013-04-18 general route cleanup
2013-04-18 cleanup of BOM
2013-04-18 remove old BOM
2013-04-18 Removed capacitor (C45) guess for link
2013-04-20 relocated BM input away from 3.3V input, added more clearance between mounting holes and USB input, added XOR gate to SBUS TX, added ground plane to top side of board
2013-04-20 layout cleanup
2013-04-20 fixed SBUS Tx connection, fixed clearance issue with updated XOR connections, added extra vias for ground
2013-04-23 moved vias away from under sensors, added more gnd vias, cleaned up BOM
2013-04-24 moved BM closer to LED control, improved grounding for LED's
2013-04-25 reverted to fixed ground plane for BM and LED GND's, moved lavels
2013-04-28 "j" version from Alfred
2013-04-28 Revert ""j" version from Alfred"
    This reverts commit dfbd99c4a951c4a7fc19233cae0e41e3843b112f.
2013-04-28 change LED connector type for normal 100mil pitch
2013-04-29 Changes from ala42 20130428
2013-04-29 Begin work on Due compatible AQ shield
2013-04-29 Isolate BM/LED GND from main GND using 0R resistor. More clearance around holes.
2013-04-30 Remove traces under mag.
2013-05-01 removing old .pdf files
2013-05-23 added camera servo pins, starting overall review of other Due pins
2013-05-27 Latest from Alfred (20130526_b)
2013-07-04 Ala42 added HMC5983 support, remapped receiver/motor lines to match v1 board, moved mag to avoid interference, made space for standoffs by moving uSD conenctor, made power lines thicker
2013-07-04 removed uSD connector ferrit bead, increased the font sizes
2013-07-10 ala42 added blocking cap for uSD (C10), updated silkscreen to v2.0.2, replaced R54 to C54 (2.2uF) for F4 compatibility

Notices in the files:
parts and their libraries:
SparkFun-Connectors: Licensing: CC v3.0 Share-Alike You are welcome to use this library for commercial purposes.
